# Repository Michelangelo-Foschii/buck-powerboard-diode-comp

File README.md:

# Programmable 28V to 3.3V Buck Power Board for Avionics Applications

This project implements a 28V to 3.3V buck regulator board using the TPS54340 and the Diode PCB DSL toolchain. The design was motivated by rocketry avionics style power distribution, where higher voltage rails often need to be stepped down for embedded electronics and control hardware. The repository includes the board definition, custom footprints, and an ngspice based simulation flow used to validate startup and switching behavior.

## Schematic View

## Layout View

The current layout captures the board structure and component integration, though routing and final placement optimization were not the focus of this stage.

## Simulation

A simplified transient simulation was performed using ngspice to verify key aspects of the buck converter behavior.

Because the TPS54340 regulator was implemented as a custom component inside the programmable board description, full device level SPICE modeling was not immediately available. As a result, the simulation focuses on validating the surrounding power stage and switching behavior rather than modeling the complete internal regulator dynamics.

The simulated circuit therefore includes the input source, switching behavior, LC output network, and load conditions that approximate the expected converter operation. This allows the simulation to capture the most important observable characteristics of the design such as startup behavior and output settling.

### Input and Output Voltage

The output waveform shows the expected startup transient before settling near the target output voltage. The switch node toggles between approximately 0V and the input rail, which is consistent with normal buck converter operation.

This simplified simulation was sufficient to quickly verify the existing power stage design before further PCB refinement.

## Project Motivation

This board was inspired by power conversion needs commonly seen in rocketry avionics systems, where a higher voltage supply must be converted into a regulated low voltage rail for onboard electronics. The design focuses on implementing a compact 28V to 3.3V switching supply and validating its behavior through simulation before further PCB refinement.

## Development Workflow

An interesting part of this project was experimenting with AI assisted engineering tools during the design process.

I used Claude Code while working with the Diode Computer PCB DSL to recreate the architecture of an existing power board used in a rocketry avionics project. The original board design, simulation, and validation process took several weeks to complete during the hardware development cycle. Using Claude Code as an interactive assistant, I was able to reproduce the overall structure of the board definition and simulation setup in a much shorter time frame.

Over the course of a few days I iteratively prompted the tool for roughly two hours each day, gradually refining the board description, component connections, and simulation setup. The tool was particularly helpful in navigating the Diode DSL toolchain and generating the boilerplate needed for the board definition.

One useful capability was the ability to integrate custom components. In this case I defined my own regulator component for the TPS54340 and connected it into the programmable board description alongside standard passive components from the library.

Overall the workflow allowed me to rapidly prototype a programmable representation of the power board and validate parts of the design using simulation.

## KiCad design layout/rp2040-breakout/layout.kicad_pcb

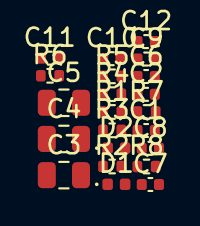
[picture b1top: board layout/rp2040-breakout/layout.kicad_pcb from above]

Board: 4 copper layers, 22 parts (0 on the bottom side), 4 nets, no tracks yet.

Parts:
C1, C2, C6, C9, C10, C11, C12: GCM155R71H104KE02D; C_0402_1005Metric
C3, C4, C5: GRM21BZ71E106KE15K; C_0805_2012Metric
C7, C8: GCM1555C1H102FA16D; C_0402_1005Metric
D1: VLMS1500-GS08; LED_0402_1005Metric
D2: VLMG1500-GS08; LED_0402_1005Metric
R1, R3, R4, R6: ERJ-2RKF1002X; R_0402_1005Metric
R2: ERJ-2RKF3300X; R_0402_1005Metric
R5: ERJ-2RKF1001X; R_0402_1005Metric
R7, R8: ERJ-2RKF4701X; R_0402_1005Metric

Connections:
3V3: C1.1, C2.1, C3.1, C5.1, C6.1, C9.1, C10.1, C11.1, C12.1, R1.1, R3.1, R4.1, R5.1, R6.1, R7.1, R8.1
FAULT_LED: D1.2, R2.1
GND: C1.2, C2.2, C3.2, C4.2, C5.2, C6.2, C7.2, C8.2, C9.2, C10.2, C11.2, C12.2, D1.1, D2.1, R2.2
LED: D2.2, R5.2

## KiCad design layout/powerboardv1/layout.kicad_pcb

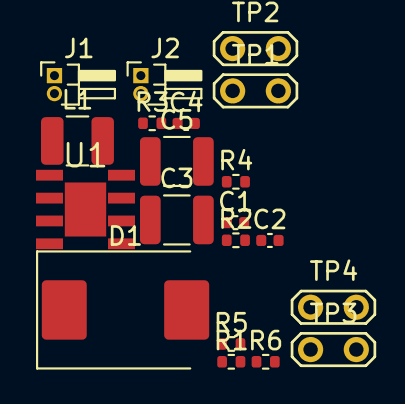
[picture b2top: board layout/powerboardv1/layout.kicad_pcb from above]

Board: 4 copper layers, 20 parts (0 on the bottom side), 9 nets, no tracks yet.

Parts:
C1, C4: GCM155R71H104KE02D; C_0402_1005Metric
C2: GRM1555CYA103GE01D; C_0402_1005Metric
C3: CGA4J1X7R1H226M125AC; C_1210_3225Metric
C5: C3216X7R1A106K160AC; C_1210_3225Metric
D1: Schottky; D_SMC
J1: INPUT_2PIN; PinHeader_1x02
J2: OUTPUT_2PIN; PinHeader_1x02
L1: 5.6uH; L_1210_3225Metric
R1: ERJ-2RKF1002X; R_0402_1005Metric
R2, R5, R6: ERJ-2RKF1003X; R_0402_1005Metric
R3: ERJ-2RKF3653X; R_0402_1005Metric
R4: ERJ-2RKF3242X; R_0402_1005Metric
TP1: TP_VIN; TestPoint
TP2: TP_GND; TestPoint
TP3: TP_SW; TestPoint
TP4: TP_3V3; TestPoint
U1: TPS54340; TPS54340_SOIC8EP

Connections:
BOOT_3V3: C1.1, U1.1
COMP_3V3: C2.1, R1.1, U1.6
EN_3V3: R2.1, R3.2, U1.3
FB_3V3: R4.1, R5.2, U1.5
GND: C2.2, C3.2, C4.2, C5.2, D1.2, J1.2, J2.2, R1.2, R2.2, R4.2, R6.2, TP2.1, U1.7, U1.9
RT_3V3: R6.1, U1.4
SW_3V3: C1.2, D1.1, L1.1, TP3.1, U1.8
VIN_28V: C3.1, C4.1, J1.1, R3.1, TP1.1, U1.2
VOUT_3V3: C5.1, J2.1, L1.2, R5.1, TP4.1

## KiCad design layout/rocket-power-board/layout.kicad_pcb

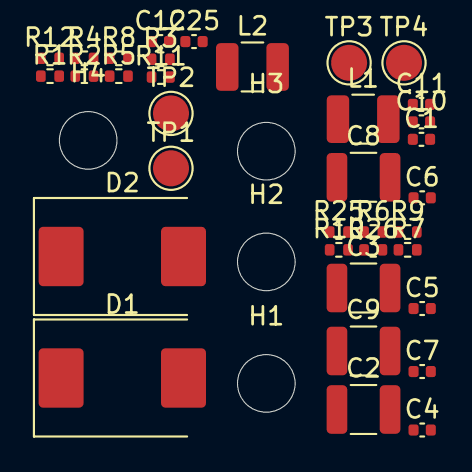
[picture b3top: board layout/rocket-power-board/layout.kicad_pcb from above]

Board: 4 copper layers, 39 parts (0 on the bottom side), 13 nets, no tracks yet.

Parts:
C1, C4, C7, C10, C25: GCM155R71H104KE02D; C_0402_1005Metric
C2, C8: 10uF; C_1210_3225Metric
C3, C9: GRM32ER71E226KE15K; C_1210_3225Metric
C5, C11: GRM1555CYA103GE01D; C_0402_1005Metric
C6, C12: GCM1555C1H101FA16D; C_0402_1005Metric
D1, D2: Schottky; D_SMC
H1, H2, H3, H4: M3 DIN965 Mechanical; MountingHole_3.2mm_M3_DIN965
L1, L2: 5.6uH; L_1210_3225Metric
R1, R4, R5, R9, R10, R11: ERJ-2RKF1003X; R_0402_1005Metric
R2, R8: ERJ-2RKF3653X; R_0402_1005Metric
R3: ERJ-2RKF3242X; R_0402_1005Metric
R6, R12: ERJ-2RKF1002X; R_0402_1005Metric
R7: ERJ-2RKF5233X; R_0402_1005Metric
R25: ERJ-2RKF3302X; R_0402_1005Metric
R26: ERJ-2RKF6802X; R_0402_1005Metric
TP1, TP2, TP3, TP4: ?; TestPoint_Pad_D2.0mm

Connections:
3V3: C2.1, C25.1, L1.2, R1.1, TP2.1
5V: C8.1, L2.2, R7.1, R25.1, TP3.1
5V_GPIO: R25.2, R26.1
28V: C3.1, C4.1, C9.1, C10.1, R2.1, R8.1, TP1.1
COMP_3V3: C5.1, C6.1, R6.1
COMP_5V: C11.1, C12.1, R12.1
EN_3V3: R2.2, R5.1
EN_5V: R8.2, R11.1
FB_3V3: R1.2, R3.1
FB_5V: R7.2, R9.1
GND: C2.2, C3.2, C4.2, C5.2, C6.2, C8.2, C9.2, C10.2, C11.2, C12.2, C25.2, D1.2, D2.2, R3.2, R4.2, R5.2, R6.2, R9.2, R10.2, R11.2, R12.2, R26.2, TP4.1
SW_3V3: C1.2, D1.1, L1.1
SW_5V: C7.2, D2.1, L2.1

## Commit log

2026-03-07 init
2026-03-11 Initial commit: programmable buck converter board + ngspice simulation
2026-03-11 Add project README
2026-03-11 Add schematic and layout screenshots
